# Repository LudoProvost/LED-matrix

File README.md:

# LED Matrix

## Schematic
The schematic has 2 parts.
1. circuit protection and voltage regulation

2. WS2812 LED 6x6 matrix

## Custom Footprints
Custom footprints for the LMS78 and the barrel jack connector were made in Fusion360

### Custom barrel jack connector:

### Custom LMS78:

## PCB editor
The KiCad PCD editor was used to design the PCB below.

3D render of the PCB with the custom footprints:

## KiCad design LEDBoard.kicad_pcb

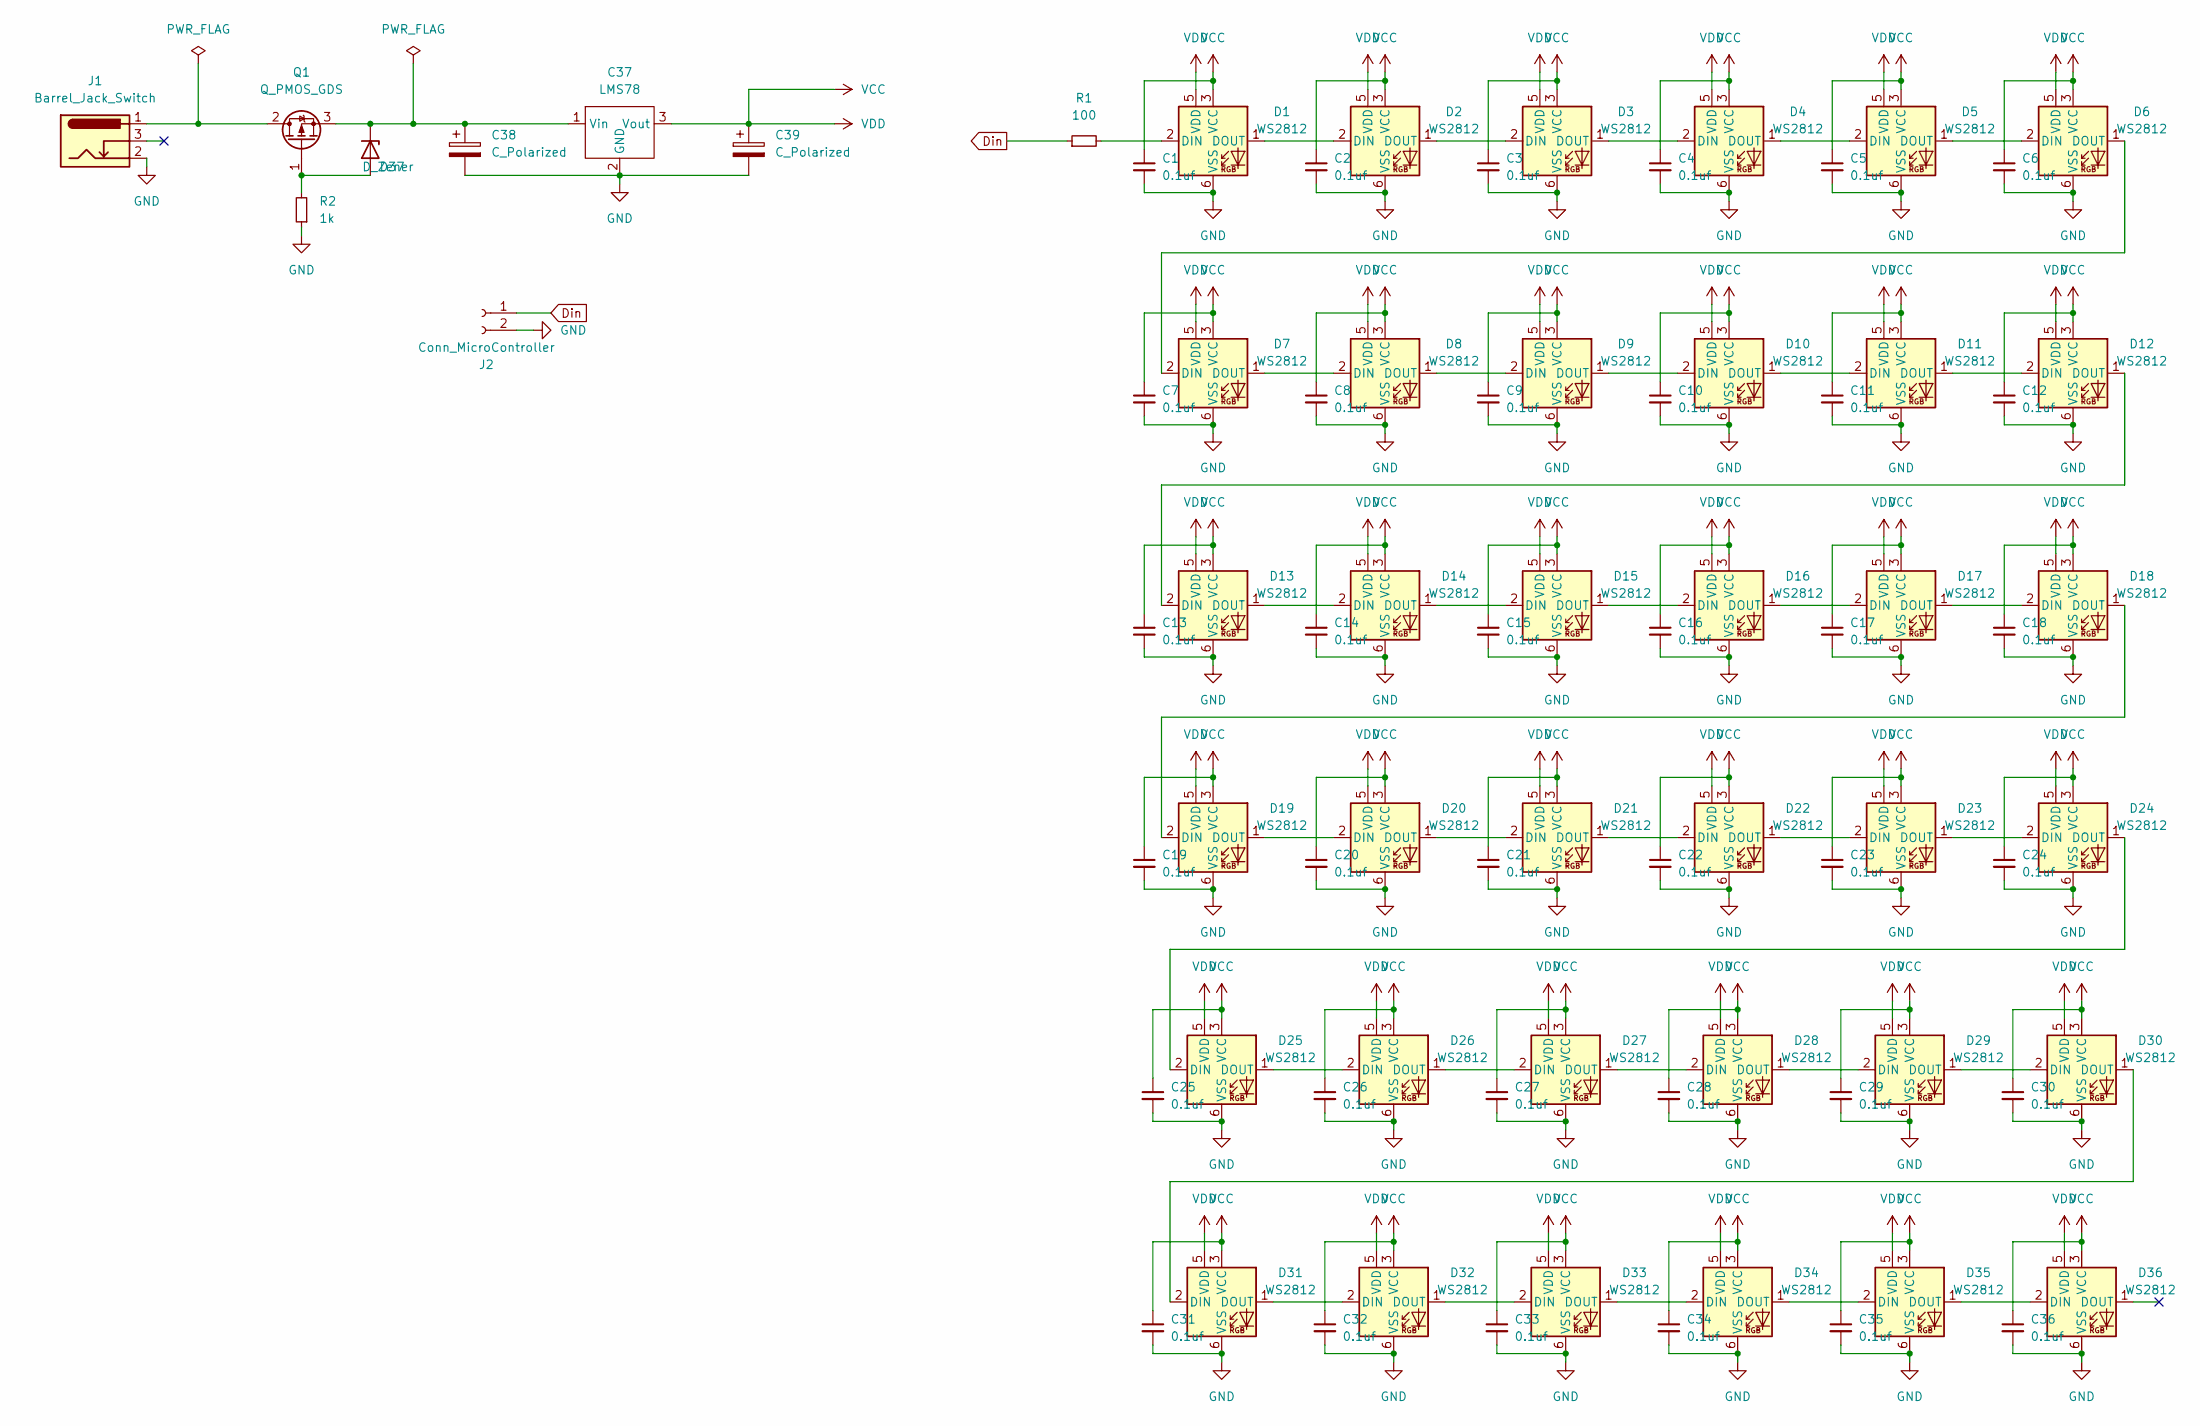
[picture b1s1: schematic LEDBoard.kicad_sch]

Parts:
C1, C2, C3, C4, C5, C6, C7, C8, C9, C10, C11, C12, C13, C14, C15, C16, C17, C18, C19, C20, C21, C22, C23, C24, C25, C26, C27, C28, C29, C30, C31, C32, C33, C34, C35, C36: 0.1uf; C_0805_2012Metric_Pad1.18x1.45mm_HandSolder
C37: LMS78
C38, C39: C_Polarized; C_1206_3216Metric_Pad1.33x1.80mm_HandSolder
D1, D2, D3, D4, D5, D6, D7, D8, D9, D10, D11, D12, D13, D14, D15, D16, D17, D18, D19, D20, D21, D22, D23, D24, D25, D26, D27, D28, D29, D30, D31, D32, D33, D34, D35, D36: WS2812; LED_WS2812_PLCC6_5.0x5.0mm_P1.6mm
D37: D_Zener; SOT-23
J1: Barrel_Jack_Switch; BarrelJack_G-1005B
J2: Conn_MicroController; PinHeader_1x02_P2.54mm_Vertical
Q1: Q_PMOS_GDS; TO-263-2
R1: 100; R_0603_1608Metric_Pad0.98x0.95mm_HandSolder
R2: 1k; R_1206_3216Metric_Pad1.30x1.75mm_HandSolder

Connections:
Din: J2.1, R1.1
GND: C1.2, C2.2, C3.2, C4.2, C5.2, C6.2, C7.2, C8.2, C9.2, C10.2, C11.2, C12.2, C13.2, C14.2, C15.2, C16.2, C17.2, C18.2, C19.2, C20.2, C21.2, C22.2, C23.2, C24.2, C25.2, C26.2, C27.2, C28.2, C29.2, C30.2, C31.2, C32.2, C33.2, C34.2, C35.2, C36.2, C37.2 (GND), C38.2, C39.2, D1.6 (VSS), D2.6 (VSS), D3.6 (VSS), D4.6 (VSS), D5.6 (VSS), D6.6 (VSS), D7.6 (VSS), D8.6 (VSS), D9.6 (VSS), D10.6 (VSS), D11.6 (VSS), D12.6 (VSS), D13.6 (VSS), D14.6 (VSS), D15.6 (VSS), D16.6 (VSS), D17.6 (VSS), D18.6 (VSS), D19.6 (VSS), D20.6 (VSS), D21.6 (VSS), D22.6 (VSS), D23.6 (VSS), D24.6 (VSS), D25.6 (VSS), D26.6 (VSS), D27.6 (VSS), D28.6 (VSS), D29.6 (VSS), D30.6 (VSS), D31.6 (VSS), D32.6 (VSS), D33.6 (VSS), D34.6 (VSS), D35.6 (VSS), D36.6 (VSS), J1.2, J2.2, R2.1
unnamed: C37.1 (Vin), C38.1, D37.3 (K), Q1.3 (S)
unnamed: D1.1 (DOUT), D2.2 (DIN)
unnamed: D1.2 (DIN), R1.2
unnamed: D2.1 (DOUT), D3.2 (DIN)
unnamed: D3.1 (DOUT), D4.2 (DIN)
unnamed: D4.1 (DOUT), D5.2 (DIN)
unnamed: D5.1 (DOUT), D6.2 (DIN)
unnamed: D6.1 (DOUT), D7.2 (DIN)
unnamed: D7.1 (DOUT), D8.2 (DIN)
unnamed: D8.1 (DOUT), D9.2 (DIN)
unnamed: D10.1 (DOUT), D11.2 (DIN)
unnamed: D9.1 (DOUT), D10.2 (DIN)
unnamed: D11.1 (DOUT), D12.2 (DIN)
unnamed: D12.1 (DOUT), D13.2 (DIN)
unnamed: D13.1 (DOUT), D14.2 (DIN)
unnamed: D14.1 (DOUT), D15.2 (DIN)
unnamed: D15.1 (DOUT), D16.2 (DIN)
unnamed: D16.1 (DOUT), D17.2 (DIN)
unnamed: D17.1 (DOUT), D18.2 (DIN)
unnamed: D18.1 (DOUT), D19.2 (DIN)
unnamed: D19.1 (DOUT), D20.2 (DIN)
unnamed: D20.1 (DOUT), D21.2 (DIN)
unnamed: D21.1 (DOUT), D22.2 (DIN)
unnamed: D22.1 (DOUT), D23.2 (DIN)
unnamed: D23.1 (DOUT), D24.2 (DIN)
unnamed: D24.1 (DOUT), D25.2 (DIN)
unnamed: D25.1 (DOUT), D26.2 (DIN)
unnamed: D26.1 (DOUT), D27.2 (DIN)
unnamed: D27.1 (DOUT), D28.2 (DIN)
unnamed: D28.1 (DOUT), D29.2 (DIN)
unnamed: D29.1 (DOUT), D30.2 (DIN)
unnamed: D30.1 (DOUT), D31.2 (DIN)
unnamed: D31.1 (DOUT), D32.2 (DIN)
unnamed: D32.1 (DOUT), D33.2 (DIN)
unnamed: D33.1 (DOUT), D34.2 (DIN)
unnamed: D34.1 (DOUT), D35.2 (DIN)
unnamed: D35.1 (DOUT), D36.2 (DIN)
unnamed: D37.1 (A), Q1.1 (G), R2.2
unnamed: J1.1, Q1.2 (D)
VCC: C1.1, C2.1, C3.1, C4.1, C5.1, C6.1, C7.1, C8.1, C9.1, C10.1, C11.1, C12.1, C13.1, C14.1, C15.1, C16.1, C17.1, C18.1, C19.1, C20.1, C21.1, C22.1, C23.1, C24.1, C25.1, C26.1, C27.1, C28.1, C29.1, C30.1, C31.1, C32.1, C33.1, C34.1, C35.1, C36.1, C37.3 (Vout), C39.1, D1.3 (VCC), D1.5 (VDD), D2.3 (VCC), D2.5 (VDD), D3.3 (VCC), D3.5 (VDD), D4.3 (VCC), D4.5 (VDD), D5.3 (VCC), D5.5 (VDD), D6.3 (VCC), D6.5 (VDD), D7.3 (VCC), D7.5 (VDD), D8.3 (VCC), D8.5 (VDD), D9.3 (VCC), D9.5 (VDD), D10.3 (VCC), D10.5 (VDD), D11.3 (VCC), D11.5 (VDD), D12.3 (VCC), D12.5 (VDD), D13.3 (VCC), D13.5 (VDD), D14.3 (VCC), D14.5 (VDD), D15.3 (VCC), D15.5 (VDD), D16.3 (VCC), D16.5 (VDD), D17.3 (VCC), D17.5 (VDD), D18.3 (VCC), D18.5 (VDD), D19.3 (VCC), D19.5 (VDD), D20.3 (VCC), D20.5 (VDD), D21.3 (VCC), D21.5 (VDD), D22.3 (VCC), D22.5 (VDD), D23.3 (VCC), D23.5 (VDD), D24.3 (VCC), D24.5 (VDD), D25.3 (VCC), D25.5 (VDD), D26.3 (VCC), D26.5 (VDD), D27.3 (VCC), D27.5 (VDD), D28.3 (VCC), D28.5 (VDD), D29.3 (VCC), D29.5 (VDD), D30.3 (VCC), D30.5 (VDD), D31.3 (VCC), D31.5 (VDD), D32.3 (VCC), D32.5 (VDD), D33.3 (VCC), D33.5 (VDD), D34.3 (VCC), D34.5 (VDD), D35.3 (VCC), D35.5 (VDD), D36.3 (VCC), D36.5 (VDD)

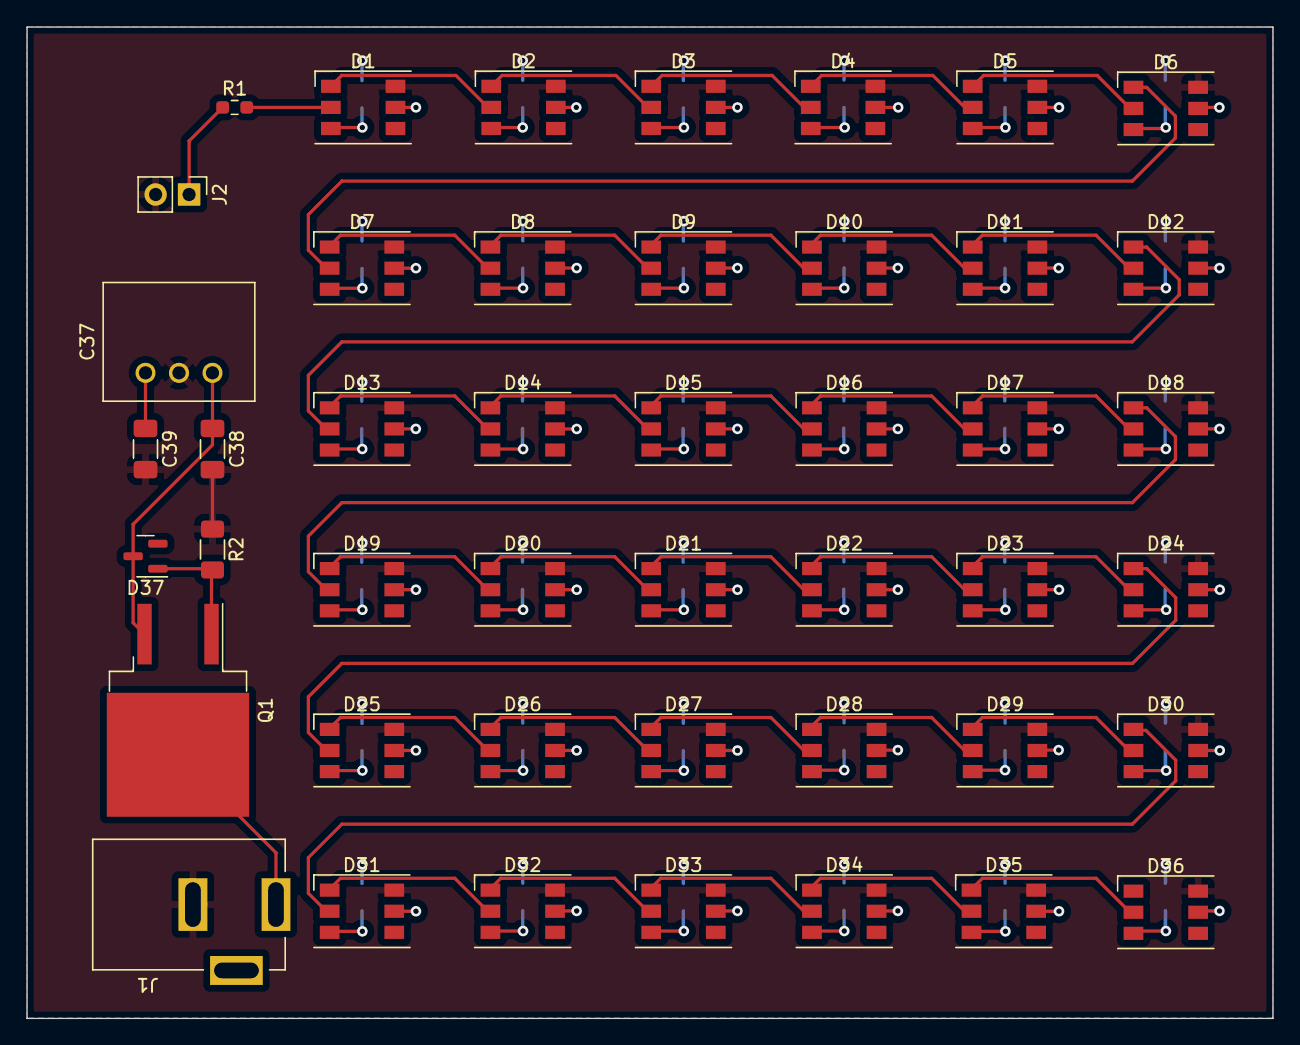
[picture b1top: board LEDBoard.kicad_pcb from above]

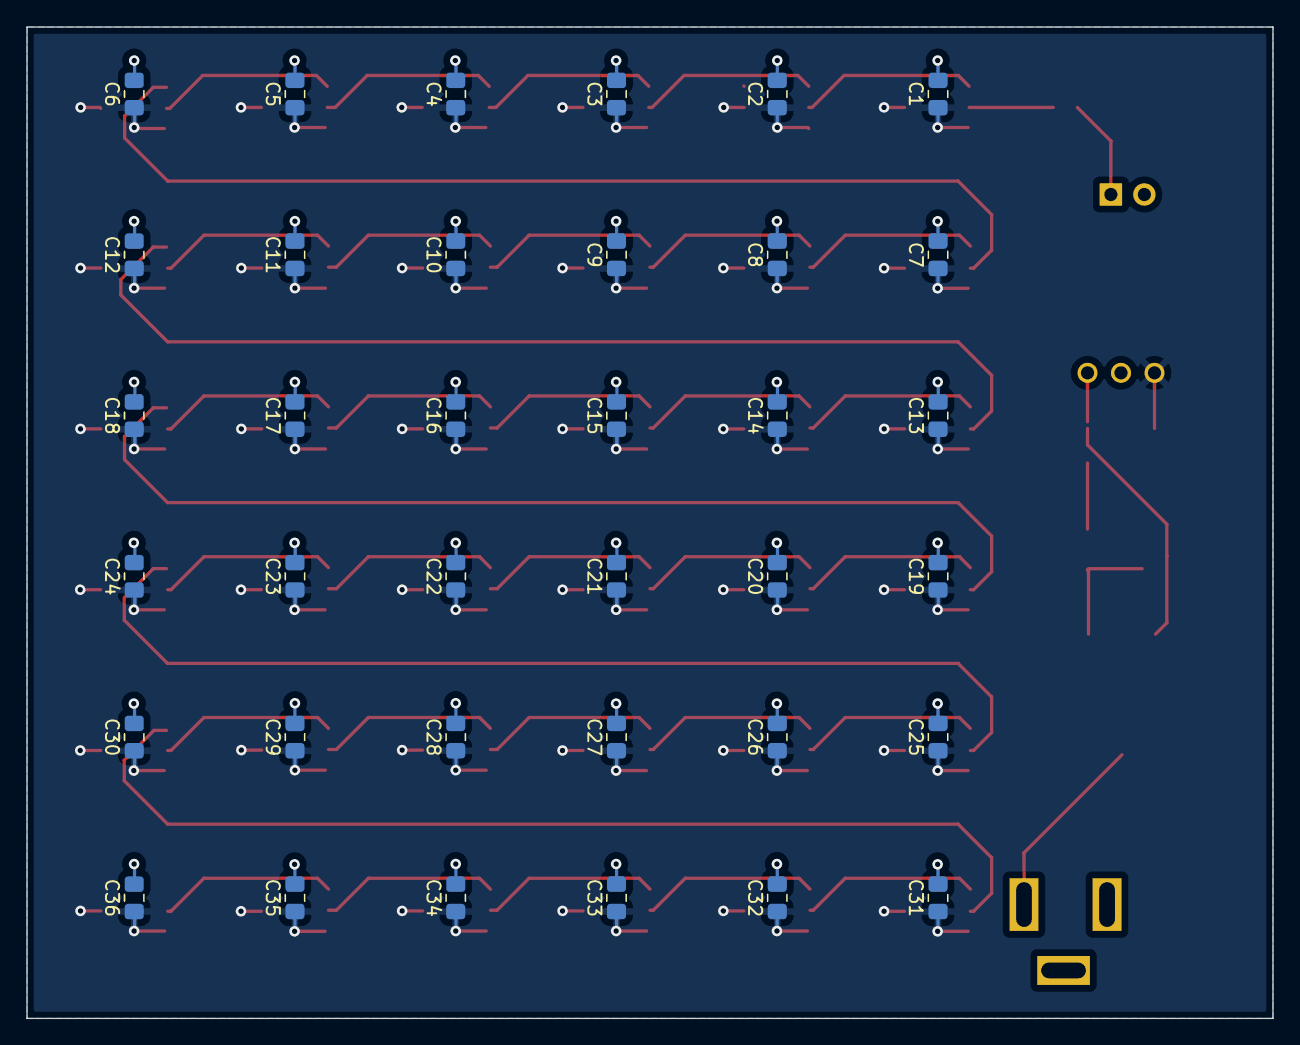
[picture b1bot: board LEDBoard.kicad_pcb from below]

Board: 2 copper layers, 94.5 x 75.2 mm, 81 parts (36 on the bottom side), 42 nets.
